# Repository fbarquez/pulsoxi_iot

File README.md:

# IoT-Based Pulse Oximeter with PIC16F1936/37 and ESP32

---

## Project Overview

This repository presents the development of a **microcontroller-based pulse oximeter** with wireless data transmission via Wi-Fi, intended for remote health monitoring. The system was designed as part of a Bachelor's thesis in **Information and Communication Technology Engineering** at HTW Berlin.

It measures **SpO₂ (blood oxygen saturation)** and **BPM (heart rate)** using optical sensing and analog signal conditioning. A **PIC16F1937** microcontroller digitizes the signals and transmits them via UART to an **ESP32-C6**, which uploads the data to **ThingSpeak** for real-time cloud visualization.

---

**View Full Thesis (Web Viewer)**: 
[Read the full thesis as images](https://fbarquez.github.io/pulsoxi_iot/docs/thesis/index.html)

**Live Demonstration Video**: 
[▶ Watch on Dropbox](https://www.dropbox.com/scl/fi/jzmq0wq67i9w6cfi0vw9p/FernandoBarrigaVasquez_videodesProjekts.mp4?rlkey=ytrc685q6z3rqatgajav5w1xa&st=frvmd6lj&dl=0)

---

## Features

- Real-time SpO₂ and BPM measurement
- Modular signal processing: sensor input, analog conditioning, digitization
- Wireless data transmission via ESP32 and Wi-Fi
- ThingSpeak dashboard with live charts
- Local LCD display for instant readings
- Custom-designed PCBs using EAGLE

---

## Folder Structure

```
├── docs/                  # Thesis report and web materials
├── firmware/              # Embedded code for PIC and ESP32
│   ├── pic/
│   └── esp32/
├── hardware/              # Schematics and PCB files
├── images/                # Photos and diagrams
├── LICENSE
├── NOTICE.md
├── README.md
└── requirements.md
```

---

## System Architecture

The system is divided into three functional modules:
...

### 1. Analog Front-End (AFE)
- **Components**: IR + Red LEDs, BPW34 photodiode
- **Signal Conditioning**: Low-pass/high-pass filters, current-to-voltage converter, amplifier

### 2. Microcontroller Unit (MCU)
- **Microcontroller**: PIC16F1937 with ADC and UART
- **Tasks**: Signal digitization, data formatting, LCD display update

### 3. Connectivity & Visualization
- **ESP32-C6**: UART receiver, Wi-Fi client
- **Cloud**: ThingSpeak channel for live plotting

---

## Hardware Design

The hardware was developed using **Autodesk EAGLE** and includes:

- Modular PCBs for:
  - Signal conditioning
  - Optical sensor input
  - Power regulation
- Schematic and board files (`.sch` / `.brd`) available in `hardware/eagle/`
- Rendered images and PDFs in `hardware/pdf/`

---

## Firmware and Software

### PIC16F1937 Firmware

- Developed in C using **MPLAB X IDE** with **MCC**
- Core features:
  - ADC configuration
  - UART transmission to ESP32
  - LCD driver integration

 Path: `firmware/pic/oxi_spo2_firmware/`

### ESP32 UART Receiver

- Written in **Arduino framework**
- Connects via UART to PIC
- Transmits data to ThingSpeak over Wi-Fi

 Path: `firmware/esp32/usart_relay_thingspeak.ino`

---

## Data Transmission & Visualization

- **ThingSpeak** IoT platform:
  - Channel with 2 fields: SpO₂ (%) and BPM
  - Real-time data plotted in the dashboard

- **LCD Output**:
  - Displays BPM and oxygen level locally

---

## Requirements

- [MPLAB X IDE](https://www.microchip.com/en-us/tools-resources/develop/mplab-x-ide)
- [MCC (Code Configurator)](https://www.microchip.com/mplab/mplab-code-configurator)
- [Arduino IDE](https://www.arduino.cc/en/software)
- ESP32 board support package
- [ThingSpeak account](https://thingspeak.com)

---

## Usage Instructions

### 1. Clone the repository

```bash
git clone https://github.com/yourusername/SpO2-Monitor-Project.git
cd SpO2-Monitor-Project
```

### 2. PIC Firmware

- Open `firmware/pic/oxi_spo2_firmware/` in MPLAB X
- Compile and flash to the PIC16F1937

### 3. ESP32 Code

- Open `firmware/esp32/usart_relay_thingspeak.ino` in Arduino IDE
- Configure your Wi-Fi credentials and ThingSpeak API key
- Upload to your ESP32 board

### 4. Dashboard

- Access your ThingSpeak channel to monitor live data
- Optionally view readings on the 16x2 LCD display

---

## License & Legal

This repository is provided **for educational and demonstration purposes only**.

> Not licensed for reuse, redistribution, or commercial use.

All content © 2024 fbarquez. 
See [`LICENSE`](LICENSE) for more details.

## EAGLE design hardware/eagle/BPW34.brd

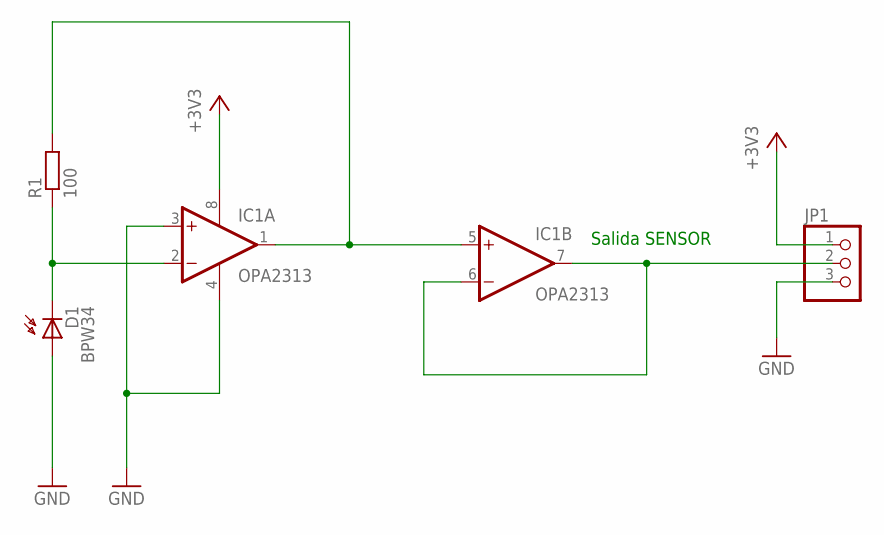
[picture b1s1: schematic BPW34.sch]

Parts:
D1: BPW34; BPW32
IC1: OPA2313; SO08
JP1: PINHD-1X3; 1X03
R1: 100; 0207/10

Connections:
+3V3: IC1.8 (V+), JP1.1
GND: D1.A, IC1.3 (+IN), IC1.4 (V-), JP1.3
unnamed: IC1.1 (OUT), IC1.5 (+IN), R1.2
unnamed: IC1.6 (-IN), IC1.7 (OUT), JP1.2
unnamed: D1.K (C), IC1.2 (-IN), R1.1

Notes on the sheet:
Salida SENSOR

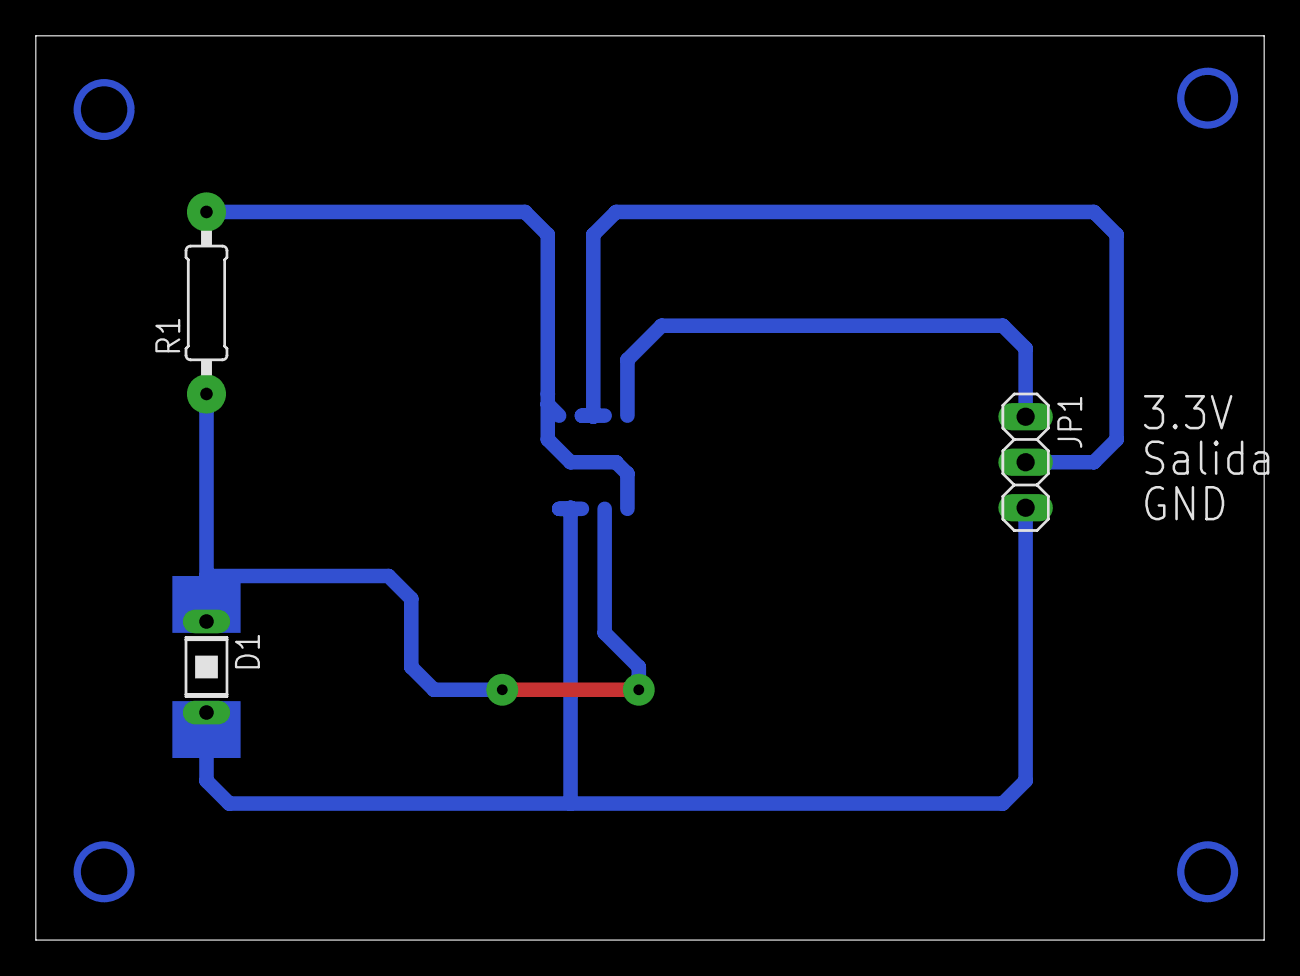
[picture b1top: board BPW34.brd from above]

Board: 2 copper layers, 68.6 x 50.5 mm, 4 parts (1 on the bottom side), 5 nets.

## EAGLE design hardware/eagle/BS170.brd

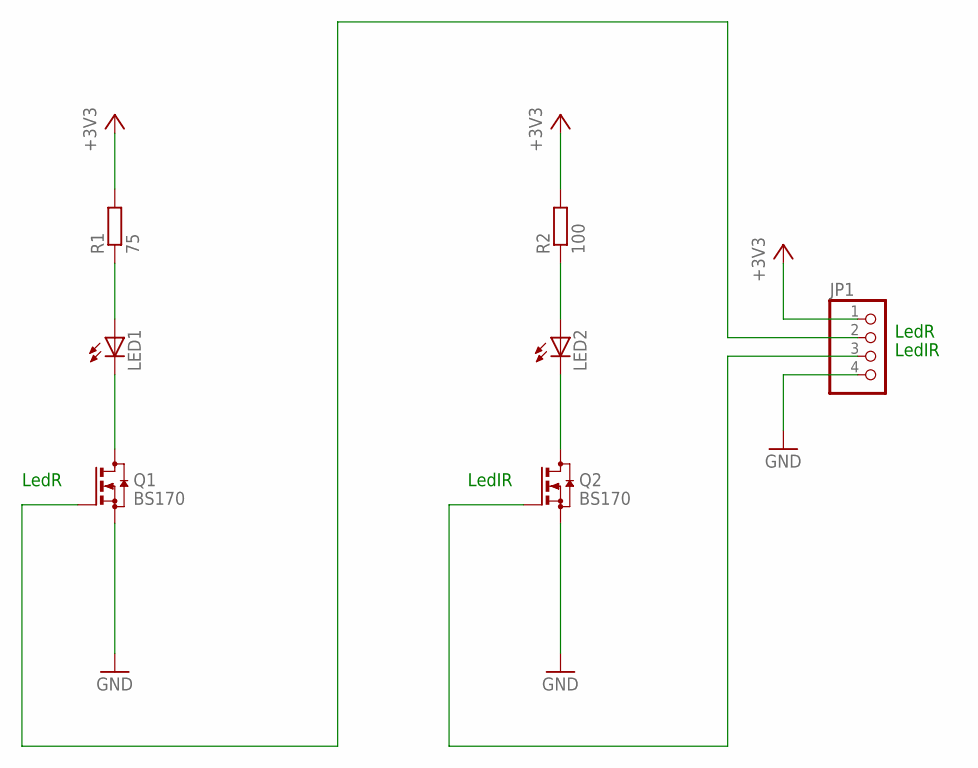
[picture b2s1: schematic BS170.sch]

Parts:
JP1: PINHD-1X4; 1X04
LED1, LED2: LED5MM
Q1, Q2: BS170; SOT23
R1: 75; 0207/10
R2: 100; 0207/10

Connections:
+3V3: JP1.1, R1.2, R2.2
GND: JP1.4, Q1.2 (S), Q2.2 (S)
unnamed: LED1.A, R1.1
unnamed: LED1.K (C), Q1.3 (D)
unnamed: LED2.A, R2.1
unnamed: LED2.K (C), Q2.3 (D)
unnamed: JP1.3, Q2.1 (G)
unnamed: JP1.2, Q1.1 (G)

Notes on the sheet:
LedIR
LedR

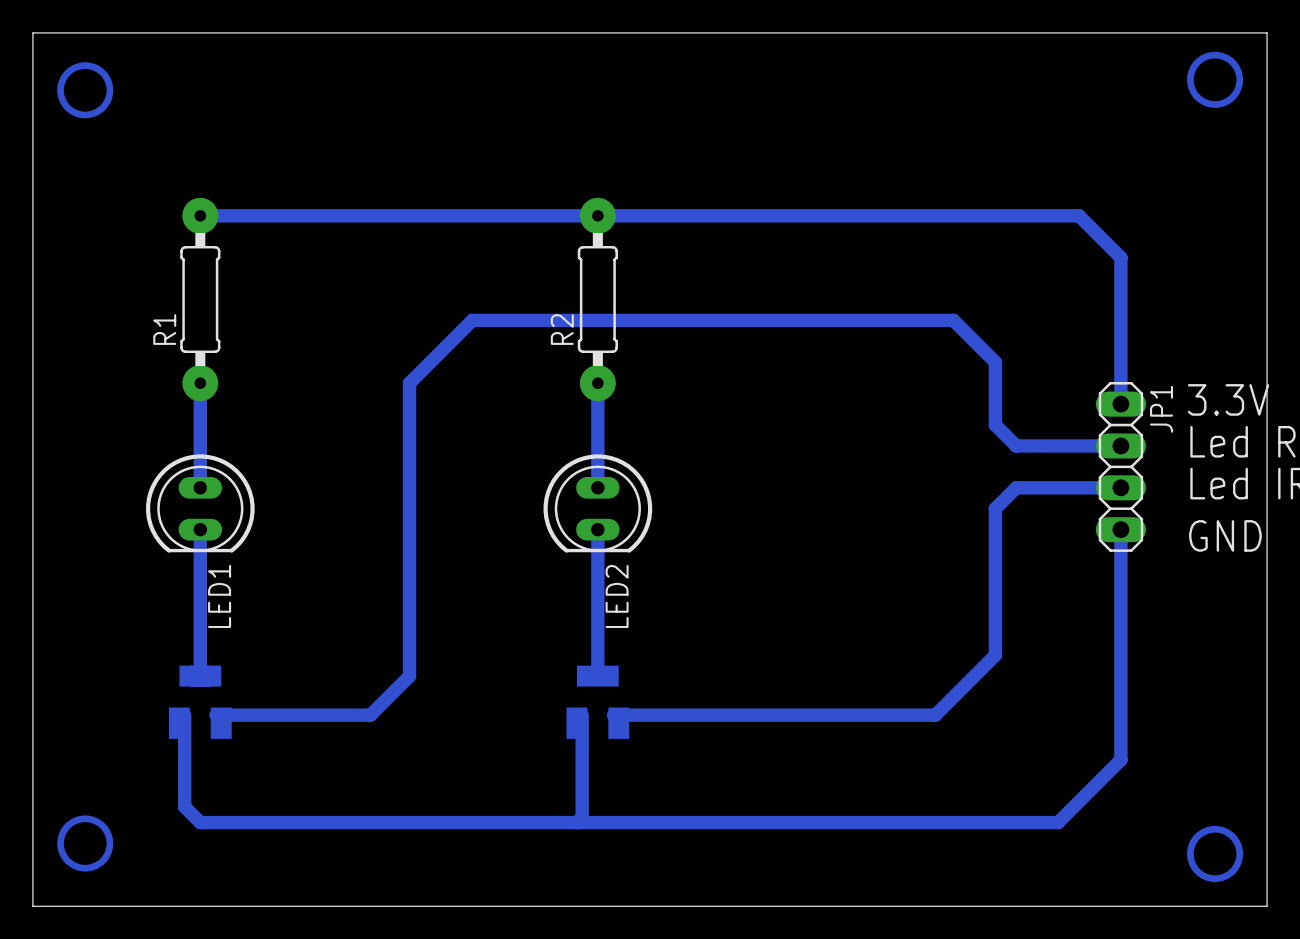
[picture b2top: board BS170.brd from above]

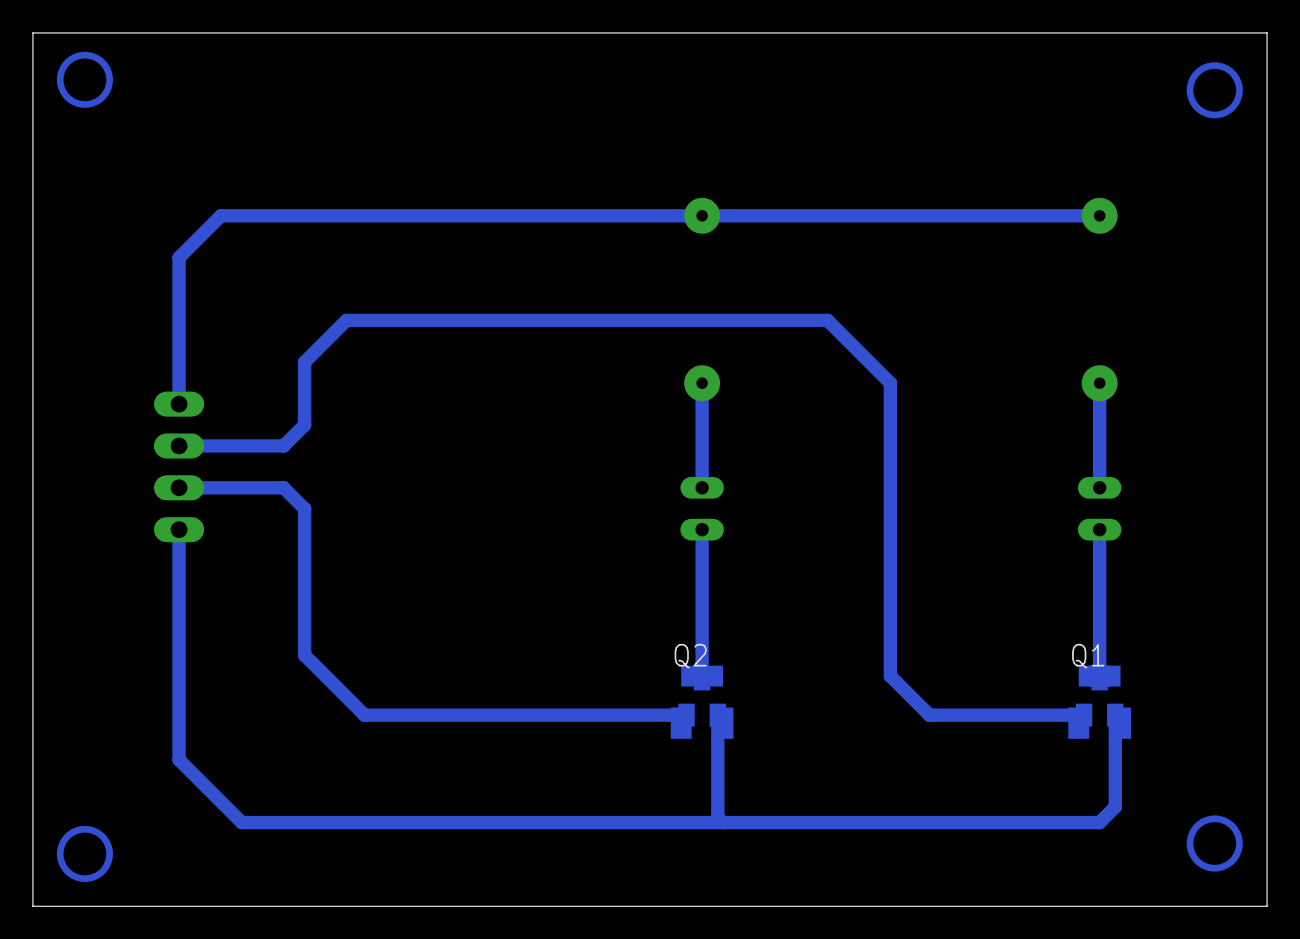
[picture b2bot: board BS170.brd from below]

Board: 2 copper layers, 74.9 x 53.0 mm, 7 parts (2 on the bottom side), 8 nets.

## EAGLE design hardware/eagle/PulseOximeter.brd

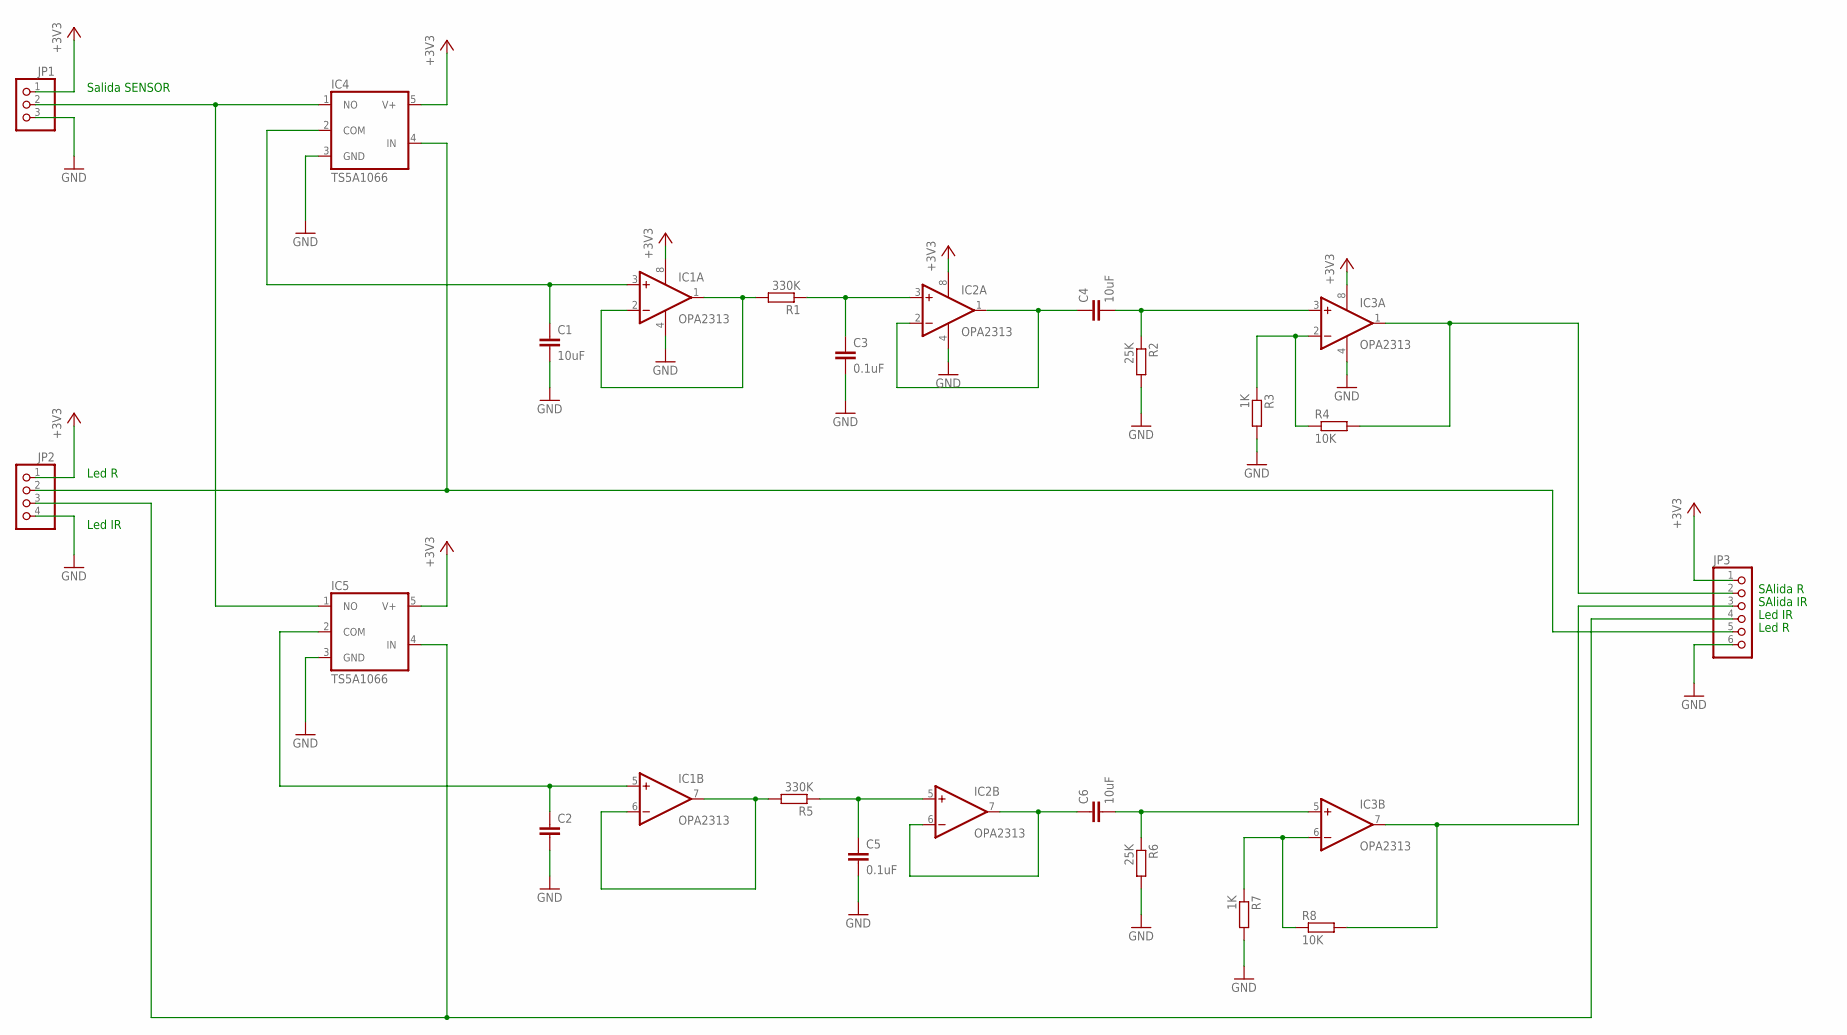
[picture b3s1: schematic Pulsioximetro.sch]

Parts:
C1, C4, C6: 10uF; C050-024X044
C2: C-EU050-024X044; C050-024X044
C3, C5: 0.1uF; C050-024X044
IC1, IC2, IC3: OPA2313; SO08
IC4, IC5: TS5A1066; SOT25
JP1: PINHD-1X3; 1X03
JP2: PINHD-1X4; 1X04
JP3: PINHD-1X6; 1X06
R1, R5: 330K; 0207/10
R2, R6: 25K; 0207/10
R3, R7: 1K; 0207/10
R4, R8: 10K; 0207/10

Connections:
+3V3: IC1.8 (V+), IC2.8 (V+), IC3.8 (V+), IC4.5 (V+), IC5.5 (V+), JP1.1, JP2.1, JP3.1
GND: C1.2, C2.2, C3.2, C5.2, IC1.4 (V-), IC2.4 (V-), IC3.4 (V-), IC4.3 (GND), IC5.3 (GND), JP1.3, JP2.4, JP3.6, R2.2, R3.2, R6.2, R7.2
unnamed: IC4.1 (NO), IC5.1 (NO), JP1.2
unnamed: IC4.4 (IN), JP2.2, JP3.5
unnamed: IC5.4 (IN), JP2.3, JP3.4
unnamed: C1.1, IC1.3 (+IN), IC4.2 (COM)
unnamed: C2.1, IC1.5 (+IN), IC5.2 (COM)
unnamed: C3.1, IC2.3 (+IN), R1.1
unnamed: IC1.1 (OUT), IC1.2 (-IN), R1.2
unnamed: C4.1, IC2.1 (OUT), IC2.2 (-IN)
unnamed: C4.2, IC3.3 (+IN), R2.1
unnamed: IC3.2 (-IN), R3.1, R4.1
unnamed: IC3.1 (OUT), JP3.2, R4.2
unnamed: IC1.6 (-IN), IC1.7 (OUT), R5.2
unnamed: C5.1, IC2.5 (+IN), R5.1
unnamed: C6.1, IC2.6 (-IN), IC2.7 (OUT)
unnamed: C6.2, IC3.5 (+IN), R6.1
unnamed: IC3.6 (-IN), R7.1, R8.1
unnamed: IC3.7 (OUT), JP3.3, R8.2

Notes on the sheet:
Salida SENSOR
Led IR
Led R
SAlida R
SAlida IR

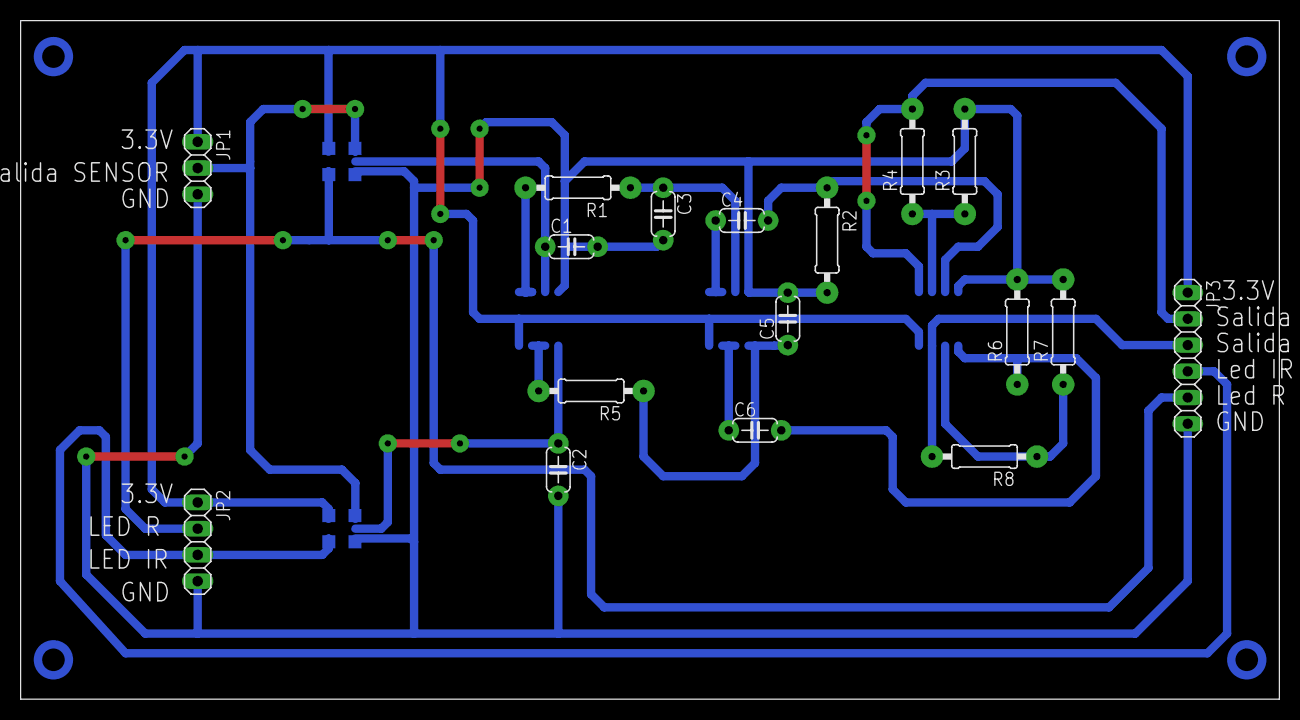
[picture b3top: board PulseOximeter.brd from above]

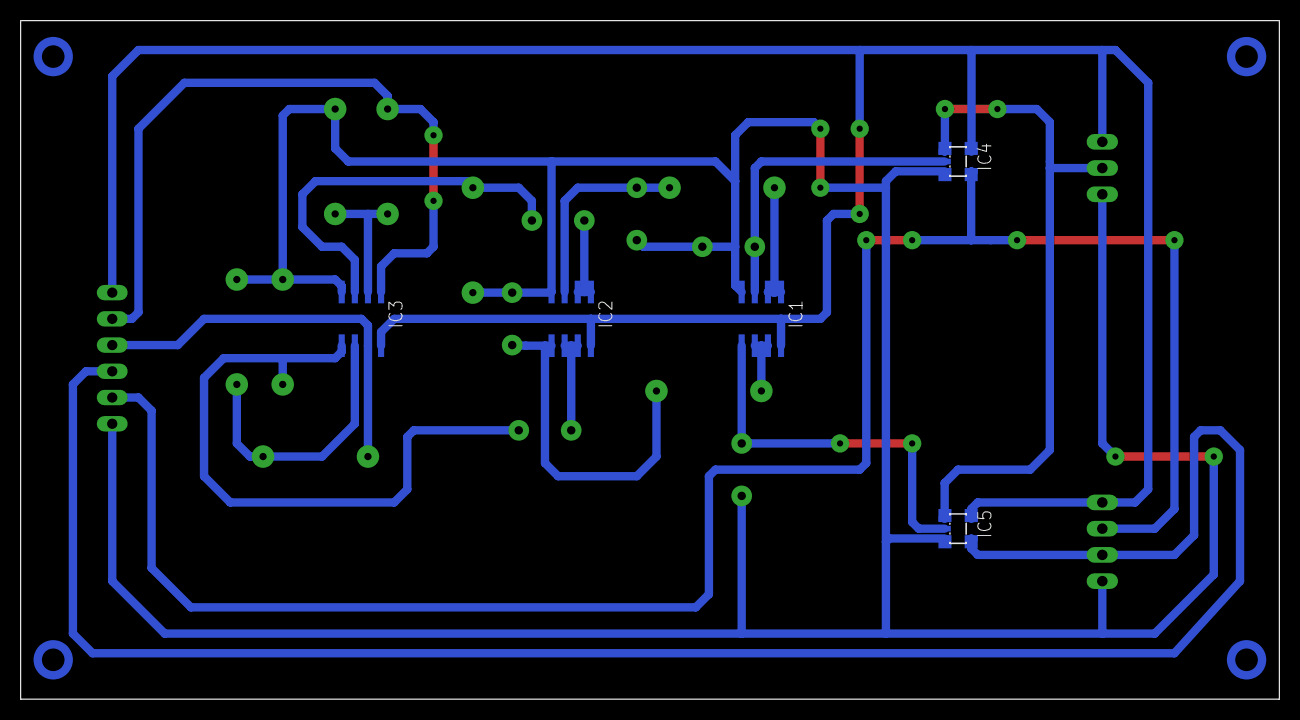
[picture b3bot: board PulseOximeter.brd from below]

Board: 2 copper layers, 121.9 x 65.7 mm, 22 parts (5 on the bottom side), 19 nets.

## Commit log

2025-05-29 Initial commit: Added firmware, web interface, diagrams and documentation
2025-05-29 update 2
2025-05-30 README
2025-05-30 favicon
2025-05-30 docs
2025-05-30 docs 2
2025-05-30 Add index.html for thesis viewer

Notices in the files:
README.md:
License: Unlicensed
